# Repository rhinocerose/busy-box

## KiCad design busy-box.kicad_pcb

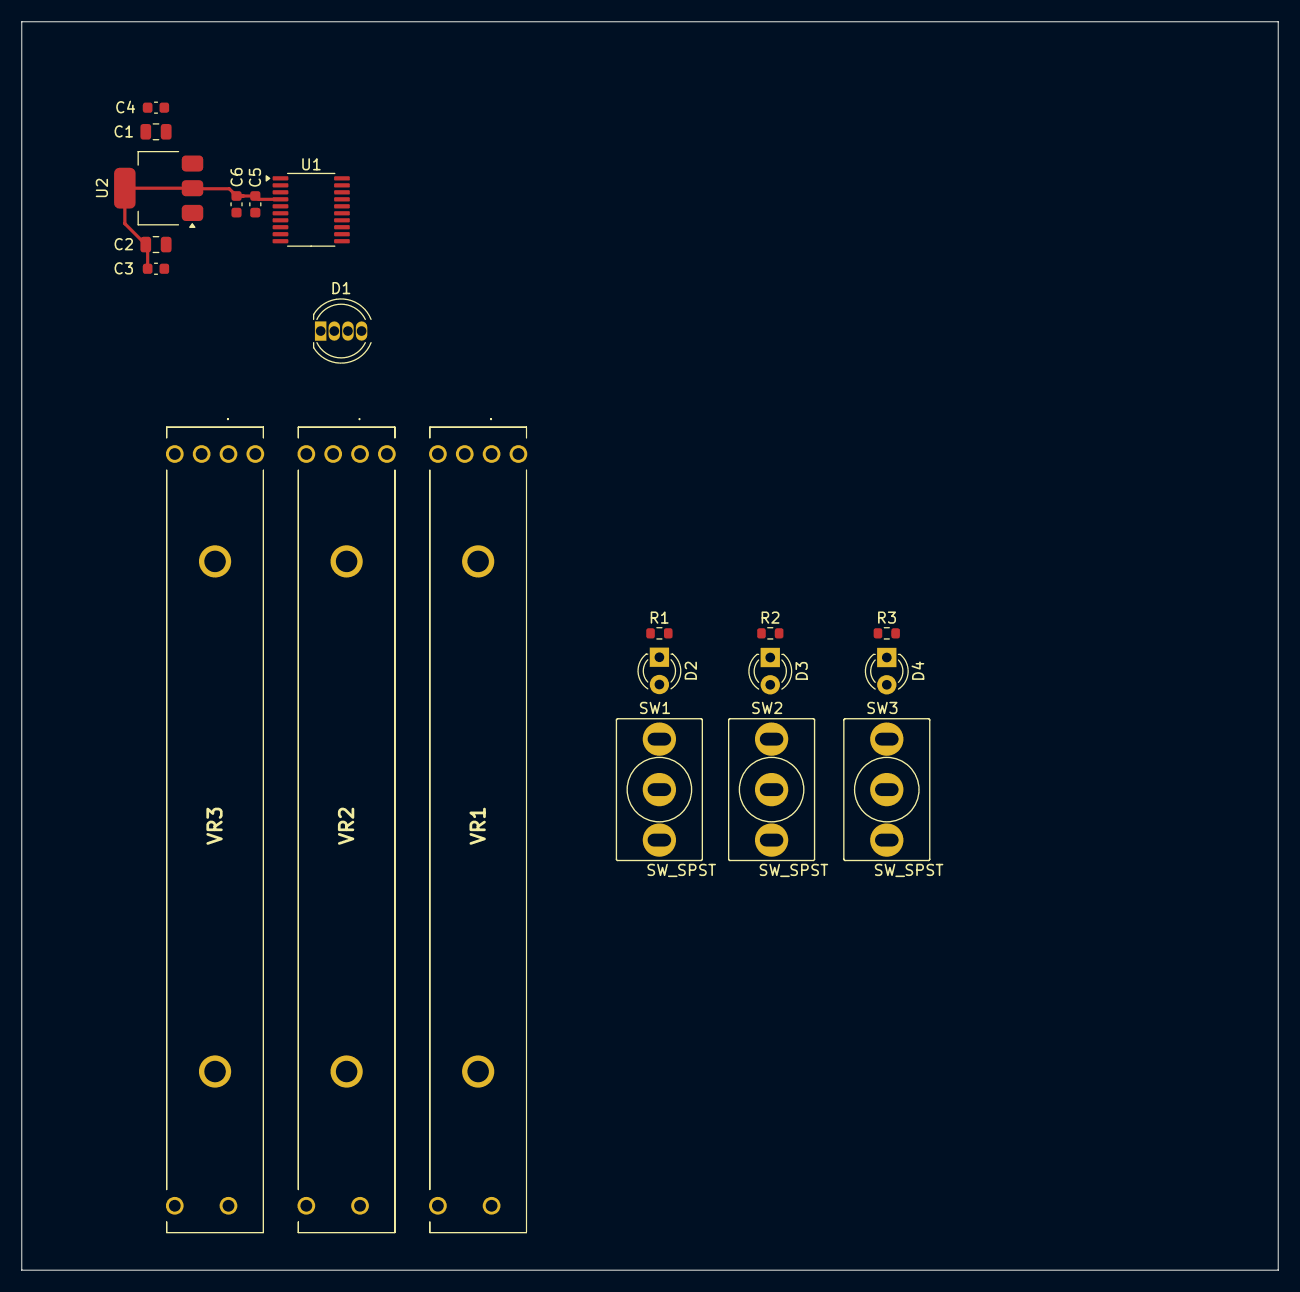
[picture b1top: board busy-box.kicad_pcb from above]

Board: 2 copper layers, 117.0 x 116.2 mm, 21 parts (0 on the bottom side), 12 nets.

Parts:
C1, C2: 10u; C_0805_2012Metric
C3, C4, C5: 100nF; C_0603_1608Metric
C6: 1uF; C_0603_1608Metric
D1: LED_KRGB; LED_D5.0mm-4_RGB
D2, D3, D4: LED; LED_D3.0mm
R1, R2, R3: R_US; R_0603_1608Metric
SW1, SW2, SW3: SW_SPST; Switch_Toggle_SPDT_Mini_SolderLug
U1: STM32G030F6Px; TSSOP-20_4.4x6.5mm_P0.65mm
U2: LM1117MP-3.3; SOT-223-3_TabPin2
VR1, VR2, VR3: Alps-Slide-Potentiometer-60mm-RS6011SP6003; Alps-Slide-Pot-60mm-RS6011SP6003

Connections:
+3.3V: C2.1, C3.1, C5.1, C6.1, SW1.2 (B), SW2.2 (B), SW3.2 (B), U1.4 (VDD), U2.2 (VO), VR1.3 (CW), VR2.3 (CW), VR3.3 (CW)
+VDC: C1.1, C4.1, U2.3 (VI)
ADC_IN_1: U1.7 (PA0), VR1.2 (WIPER)
ADC_IN_2: U1.8 (PA1), VR2.2 (WIPER)
ADC_IN_3: U1.9 (PA2), VR3.2 (WIPER)
GND: C1.2, C2.2, C3.2, C4.2, C5.2, C6.2, D1.1 (K), R1.2, R2.2, R3.2, U1.5 (VSS), U2.1 (GND), VR1.1 (CCW), VR1.L1 (LUG_TERMINAL_1), VR1.L2 (LUG_TERMINAL_2), VR1.L3 (LUG_TERMINAL_3), VR1.MH1, VR1.MH2, VR2.1 (CCW), VR2.L1 (LUG_TERMINAL_1), VR2.L2 (LUG_TERMINAL_2), VR2.L3 (LUG_TERMINAL_3), VR2.MH1, VR2.MH2, VR3.1 (CCW), VR3.L1 (LUG_TERMINAL_1), VR3.L2 (LUG_TERMINAL_2), VR3.L3 (LUG_TERMINAL_3), VR3.MH1, VR3.MH2
unnamed: D2.2 (A), SW1.1 (A)
unnamed: D2.1 (K), R1.1
unnamed: D3.2 (A), SW2.1 (A)
unnamed: D3.1 (K), R2.1
unnamed: D4.2 (A), SW3.1 (A)
unnamed: D4.1 (K), R3.1

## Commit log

2025-11-19 Added files
2025-12-03 Added sliders
2025-12-03 Organized into folders
